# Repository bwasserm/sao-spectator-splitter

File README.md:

# A splitter to turn one SAO ports into two

Expands a single Simple Add-On port on your conference badge into two ports for small SAOs.

Looks like a cute version of the smaller cousin of everyone's favorite anti-magic ray-slinging floating eyeball monster.

There's no power protection here, so only use small SAOs that won't use the full 250mA available from the source badge. Most SAOs don't use that much, so I figure this should be viable.

I've wanted to make a SAO splitter for a while. Deciding on the artistic form-factor was the hard part. I will claim I am partially inspired by the Beholder SAO I got at Supercon last year from Zachary Peterson (znjp), although since my KiCAD skills are more limited, I opted for a simpler design with fewer blinding LED beam attacks. Also, I'm in a rush and want this to work on the first try.

Simple Add-On v2 standard: https://docs.google.com/document/u/0/d/1EJqvkkLMAPsQ9VWF5A4elWoi0qMlKyr5Giw5rqRmtnM/mobilebasic?pli=1
OSHW logo from https://oshwa.org/resources/open-source-hardware-logo/
Spectator is owned by Wizards of the Coast: https://www.dndbeyond.com/monsters/17094-spectator

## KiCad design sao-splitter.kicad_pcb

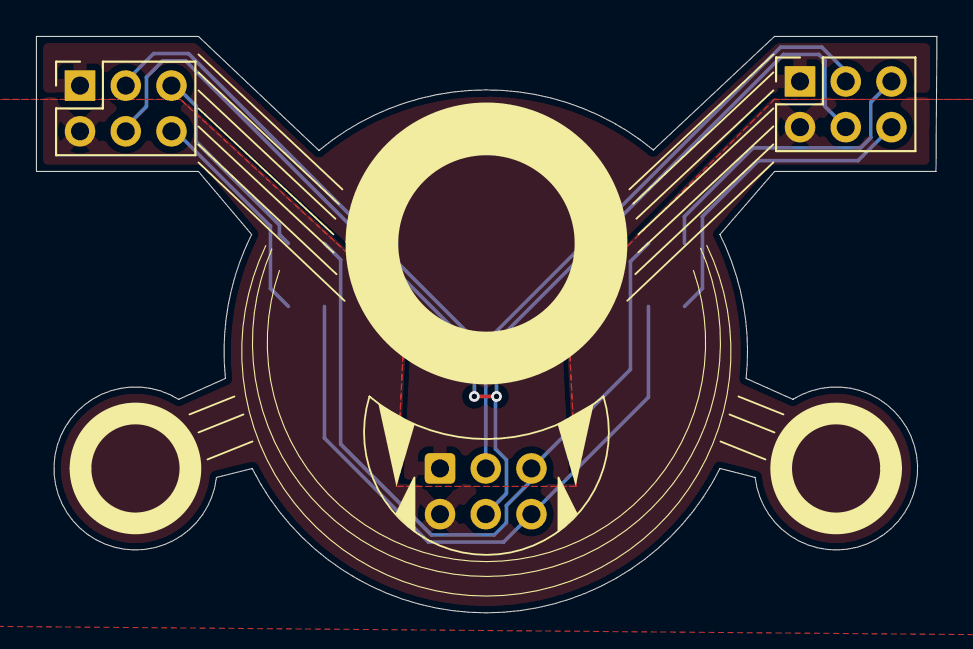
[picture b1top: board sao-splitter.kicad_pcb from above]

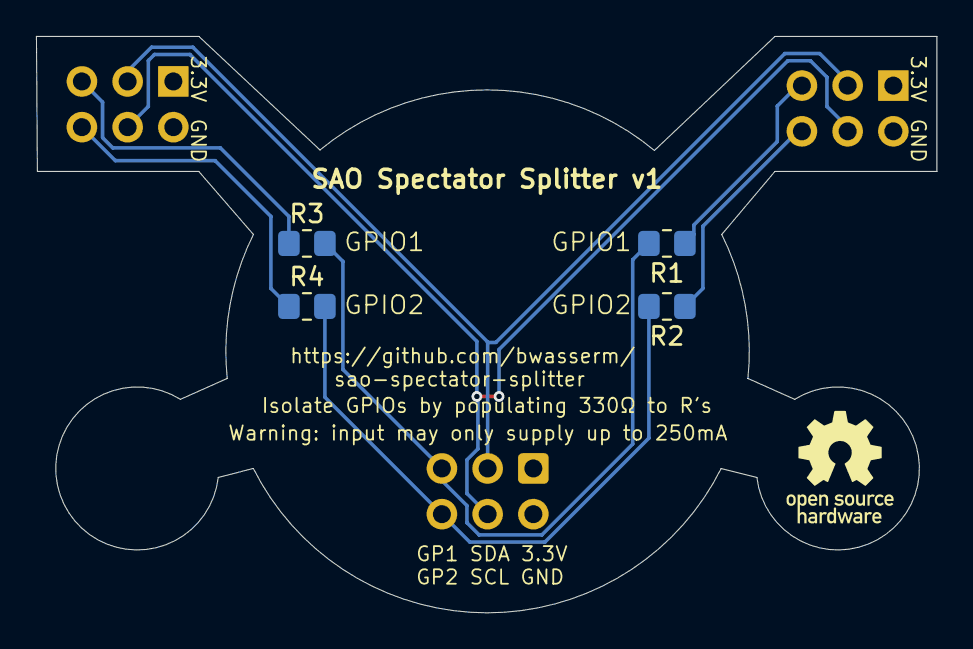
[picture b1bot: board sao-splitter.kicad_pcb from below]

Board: 2 copper layers, 50.0 x 32.0 mm, 7 parts (5 on the bottom side), 10 nets.

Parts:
J1: IDC-Header_2x03_P2.54mm_Vertical_SilkscreenHidden
J2, J3: PinSocket_2x03_P2.54mm_Vertical
R1, R2, R3: 330Ω; R_0805_2012Metric_Pad1.20x1.40mm_HandSolder
R4: All R's are rec 330Ω to isolate multiple SAOs' GP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; R_0805_2012Metric_Pad1.20x1.40mm_HandSolder

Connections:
/3V3: J1.1, J2.1, J3.1
/GND: J1.2, J2.2, J3.2
/GP1: J1.5, R1.2, R3.2
/GP2: J1.6, R2.2, R4.2
/SCL: J1.4, J2.4, J3.4
/SDA: J1.3, J2.3, J3.3
unnamed: J2.5, R1.1
unnamed: J2.6, R2.1
unnamed: J3.5, R3.1
unnamed: J3.6, R4.1
